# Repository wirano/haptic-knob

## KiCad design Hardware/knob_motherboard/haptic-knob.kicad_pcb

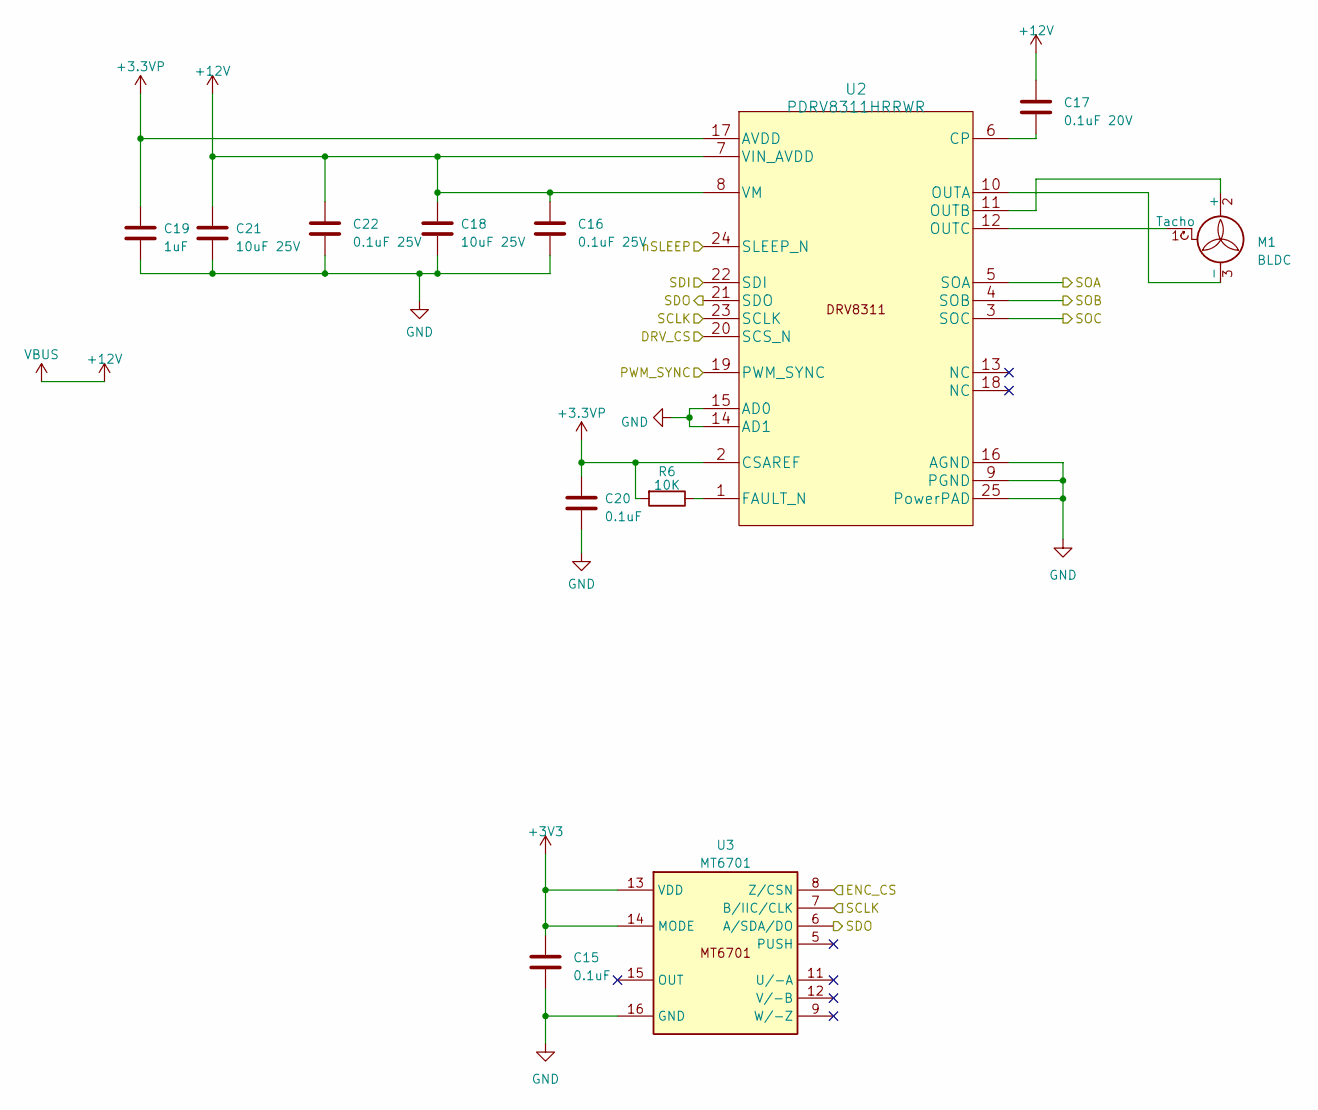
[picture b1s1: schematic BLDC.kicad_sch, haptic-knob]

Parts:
C15, C20: 0.1uF; C_0402_1005Metric
C16, C22: 0.1uF 25V; C_0402_1005Metric
C17: 0.1uF 20V; C_0402_1005Metric
C18, C21: 10uF 25V; C_0603_1608Metric
C19: 1uF; C_0402_1005Metric
M1: BLDC; JST_SH_BM03B-SRSS-TB_1x03-1MP_P1.00mm_Vertical
R6: 10K; R_0402_1005Metric
U2: PDRV8311HRRWR
U3: MT6701; QFN-16-1EP_3x3mm_P0.5mm_EP1.7x1.7mm

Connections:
+3.3VP: C19.1, C20.1, R6.2, U2.2 (CSAREF), U2.17 (AVDD)
+3V3: C15.1, U3.13 (VDD), U3.14 (MODE); also elsewhere on the board
+12V: C16.1, C17.1, C18.1, C21.1, C22.1, U2.7 (VIN_AVDD), U2.8 (VM); also elsewhere on the board
/BLDC/DRV_CS: U2.20 (SCS_N); also elsewhere on the board
/BLDC/ENC_CS: U3.8 (Z/CSN); also elsewhere on the board
/BLDC/PWM_SYNC: U2.19 (PWM_SYNC); also elsewhere on the board
/BLDC/SCLK: U2.23 (SCLK), U3.7 (B/IIC/CLK); also elsewhere on the board
/BLDC/SDI: U2.22 (SDI); also elsewhere on the board
/BLDC/SDO: U2.21 (SDO), U3.6 (A/SDA/DO); also elsewhere on the board
/BLDC/nSLEEP: U2.24 (SLEEP_N); also elsewhere on the board
/Core/SOA: U2.5 (SOA); also elsewhere on the board
/Core/SOB: U2.4 (SOB); also elsewhere on the board
/Core/SOC: U2.3 (SOC); also elsewhere on the board
GND: C15.2, C16.2, C18.2, C19.2, C20.2, C21.2, C22.2, M1.MP, U2.9 (PGND), U2.14 (AD1), U2.15 (AD0), U2.16 (AGND), U2.25 (PowerPAD), U2.26, U2.27, U2.28, U2.29, U2.30, U3.16 (GND), U3.17; also elsewhere on the board
unnamed: M1.2 (+), U2.11 (OUTB)
unnamed: M1.3 (-), U2.10 (OUTA)
unnamed: M1.1 (Tacho), U2.12 (OUTC)
unnamed: C17.2, U2.6 (CP)
unnamed: R6.1, U2.1 (FAULT_N)

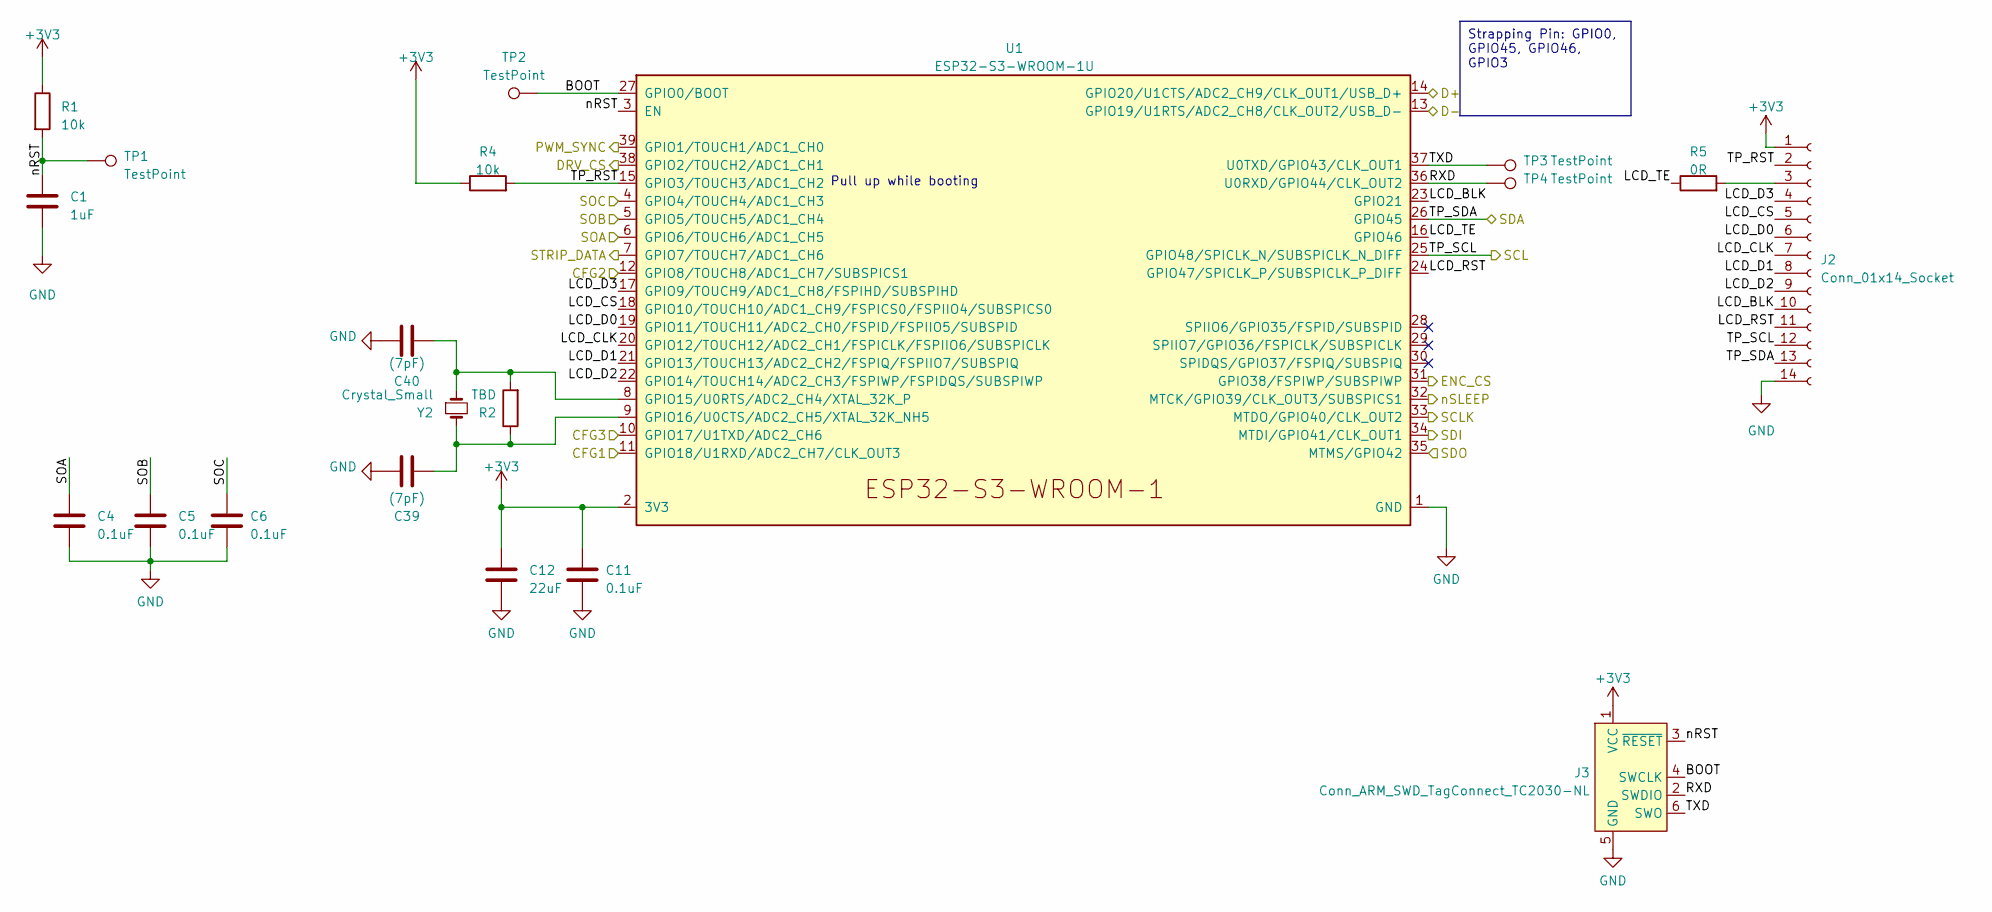
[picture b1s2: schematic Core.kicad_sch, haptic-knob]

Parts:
C1: 1uF; C_0402_1005Metric
C4, C5, C6, C11: 0.1uF; C_0402_1005Metric
C12: 22uF; C_0402_1005Metric
C39, C40: (7pF); C_0402_1005Metric
J2: Conn_01x14_Socket; JST_SHL_SM14B-SHLS-TF_1x14-1MP_P1.00mm_Horizontal
J3: Conn_ARM_SWD_TagConnect_TC2030-NL; Tag-Connect_TC2030-IDC-NL_2x03_P1.27mm_Vertical
R1, R4: 10k; R_0402_1005Metric
R2: TBD; R_0402_1005Metric
R5: 0R; R_0402_1005Metric
TP1, TP2, TP3, TP4: TestPoint; TestPoint_Pad_D1.5mm
U1: ESP32-S3-WROOM-1U
Y2: Crystal_Small; Crystal_SMD_2012-2Pin_2.0x1.2mm

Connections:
+3V3: C11.1, C12.1, J2.1, J3.1 (VCC), R1.1, R4.1, U1.2 (3V3); also elsewhere on the board
/BLDC/DRV_CS: U1.38 (GPIO2/TOUCH2/ADC1_CH1); also elsewhere on the board
/BLDC/ENC_CS: U1.31 (GPIO38/FSPIWP/SUBSPIWP); also elsewhere on the board
/BLDC/PWM_SYNC: U1.39 (GPIO1/TOUCH1/ADC1_CH0); also elsewhere on the board
/BLDC/SCLK: U1.33 (MTDO/GPIO40/CLK_OUT2); also elsewhere on the board
/BLDC/SDI: U1.34 (MTDI/GPIO41/CLK_OUT1); also elsewhere on the board
/BLDC/SDO: U1.35 (MTMS/GPIO42); also elsewhere on the board
/BLDC/nSLEEP: U1.32 (MTCK/GPIO39/CLK_OUT3/SUBSPICS1); also elsewhere on the board
/Core/BOOT: J3.4 (SWCLK), TP2.1, U1.27 (GPIO0/BOOT)
/Core/CFG1: U1.10 (GPIO17/U1TXD/ADC2_CH6); also elsewhere on the board
/Core/CFG2: U1.11 (GPIO18/U1RXD/ADC2_CH7/CLK_OUT3); also elsewhere on the board
/Core/CFG3: U1.12 (GPIO8/TOUCH8/ADC1_CH7/SUBSPICS1); also elsewhere on the board
/Core/D+: U1.14 (GPIO20/U1CTS/ADC2_CH9/CLK_OUT1/USB_D+); also elsewhere on the board
/Core/D-: U1.13 (GPIO19/U1RTS/ADC2_CH8/CLK_OUT2/USB_D-); also elsewhere on the board
/Core/LCD_BLK: J2.10, U1.23 (GPIO21)
/Core/LCD_CLK: J2.7, U1.20 (GPIO12/TOUCH12/ADC2_CH1/FSPICLK/FSPIIO6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)
/Core/LCD_CS: J2.5, U1.18 (GPIO10/TOUCH10/ADC1_CH9/FSPICS0/FSPIIO4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)
/Core/LCD_D0: J2.6, U1.19 (GPIO11/TOUCH11/ADC2_CH0/FSPID/FSPIIO5/S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)
/Core/LCD_D1: J2.8, U1.21 (GPIO13/TOUCH13/ADC2_CH2/FSPIQ/FSPIIO7/S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)
/Core/LCD_D2: J2.9, U1.22 (GPIO14/TOUCH14/ADC2_CH3/FSPIWP/FSPIDQS/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)
/Core/LCD_D3: J2.4, U1.17 (GPIO9/TOUCH9/ADC1_CH8/FSPIHD/SUBSPIHD)
/Core/LCD_RST: J2.11, U1.24 (GPIO47/SPICLK_P/SUBSPICLK_P_DIFF)
/Core/LCD_TE: R5.1, U1.16 (GPIO46)
/Core/RXD: J3.2 (SWDIO), TP4.1, U1.36 (U0RXD/GPIO44/CLK_OUT2)
/Core/SOA: C4.1, U1.6 (GPIO6/TOUCH6/ADC1_CH5); also elsewhere on the board
/Core/SOB: C5.1, U1.5 (GPIO5/TOUCH5/ADC1_CH4); also elsewhere on the board
/Core/SOC: C6.1, U1.4 (GPIO4/TOUCH4/ADC1_CH3); also elsewhere on the board
/Core/STRIP_DATA: U1.7 (GPIO7/TOUCH7/ADC1_CH6); also elsewhere on the board
/Core/TP_RST: J2.2, R4.2, U1.15 (GPIO3/TOUCH3/ADC1_CH2)
/Core/TP_SCL: J2.12, U1.25 (GPIO48/SPICLK_N/SUBSPICLK_N_DIFF); also elsewhere on the board
/Core/TP_SDA: J2.13, U1.26 (GPIO45); also elsewhere on the board
/Core/TXD: J3.6 (SWO), TP3.1, U1.37 (U0TXD/GPIO43/CLK_OUT1)
/Core/nRST: C1.1, J3.3 (~RESET), R1.2, TP1.1, U1.3 (EN)
GND: C1.2, C4.2, C5.2, C6.2, C11.2, C12.2, J2.14, J2.MP, J3.5 (GND), U1.1 (GND), U1.40 (GND), U1.41 (GND); also elsewhere on the board
unnamed: J2.3, R5.2
unnamed 49: R2.2, U1.8 (GPIO15/U0RTS/ADC2_CH4/XTAL_32K_P); also elsewhere on the board
unnamed 50: R2.1, U1.9 (GPIO16/U0CTS/ADC2_CH5/XTAL_32K_NH5); also elsewhere on the board

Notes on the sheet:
Strapping Pin: GPIO0, GPIO45, GPIO46, GPIO3
Pull up while booting

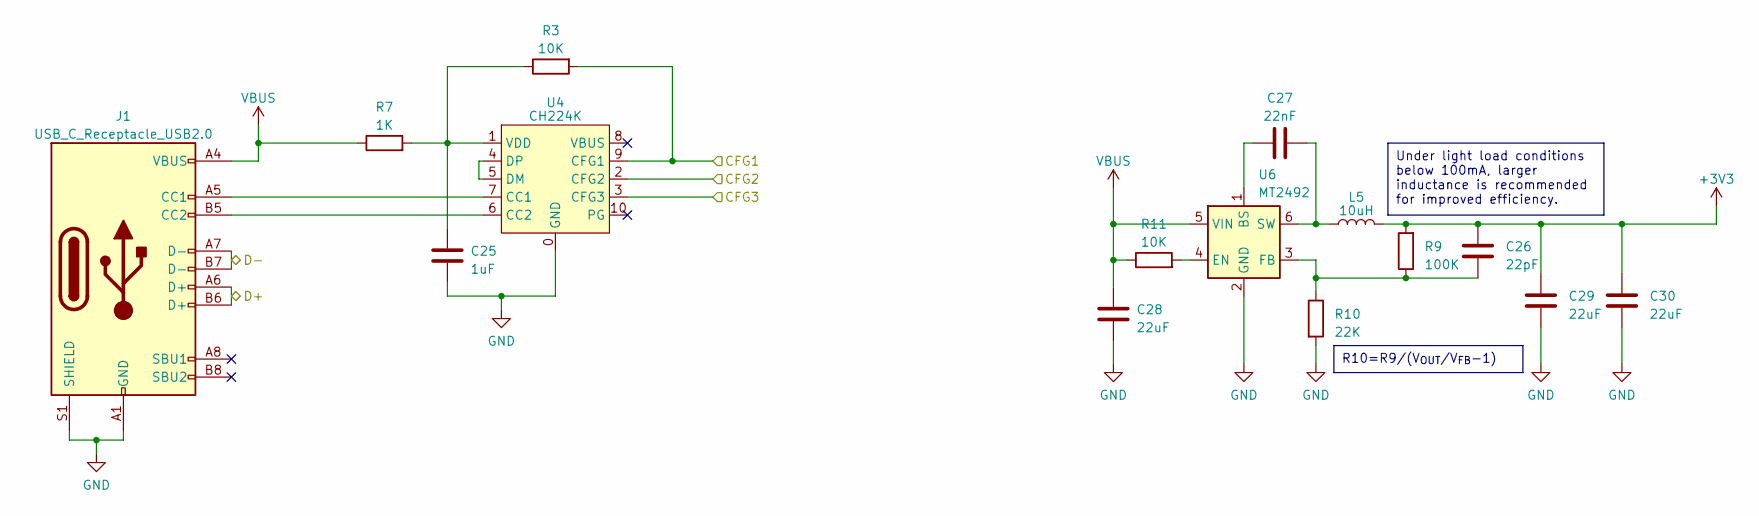
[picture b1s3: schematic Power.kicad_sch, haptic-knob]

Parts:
C25: 1uF; C_0402_1005Metric
C26: 22pF; C_0402_1005Metric
C27: 22nF; C_0402_1005Metric
C28, C29, C30: 22uF; C_0805_2012Metric
J1: USB_C_Receptacle_USB2.0; USB_C_Receptacle_XKB_U262-16XN-4BVC11
L5: 10uH; L_Sunlord_SWPA3015S
R3, R11: 10K; R_0402_1005Metric
R7: 1K; R_0402_1005Metric
R9: 100K; R_0402_1005Metric
R10: 22K; R_0402_1005Metric
U4: CH224K; ESSOP-10_3.9x4.9mm_P1.00mm_EP2.3x3.2mm
U6: MT2492; SOT-23-6

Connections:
+3V3: C26.2, C29.1, C30.1, L5.2, R9.2; also elsewhere on the board
+12V: C28.1, J1.A4 (VBUS), J1.A9 (VBUS), J1.B4 (VBUS), J1.B9 (VBUS), R7.1, R11.1, U6.5 (VIN); also elsewhere on the board
/Core/CFG1: R3.2, U4.9 (CFG1); also elsewhere on the board
/Core/CFG2: U4.2 (CFG2); also elsewhere on the board
/Core/CFG3: U4.3 (CFG3); also elsewhere on the board
/Core/D+: J1.A6 (D+), J1.B6 (D+); also elsewhere on the board
/Core/D-: J1.A7 (D-), J1.B7 (D-); also elsewhere on the board
GND: C25.2, C28.2, C29.2, C30.2, J1.A1 (GND), J1.A12 (GND), J1.B1 (GND), J1.B12 (GND), J1.S1 (SHIELD), R10.2, U4.0 (GND), U6.2 (GND); also elsewhere on the board
unnamed: J1.A5 (CC1), U4.7 (CC1)
unnamed: J1.B5 (CC2), U4.6 (CC2)
unnamed: U4.4 (DP), U4.5 (DM)
unnamed: C25.1, R3.1, R7.2, U4.1 (VDD)
unnamed: C27.1, U6.1 (BS)
unnamed: R11.2, U6.4 (EN)
unnamed: C26.1, R9.1, R10.1, U6.3 (FB)
unnamed: C27.2, L5.1, U6.6 (SW)

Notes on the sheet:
R10=R9/(V_{OUT}/V_{FB}-1)
Under light load conditions below 100mA, larger inductance is recommended for improved efficiency.

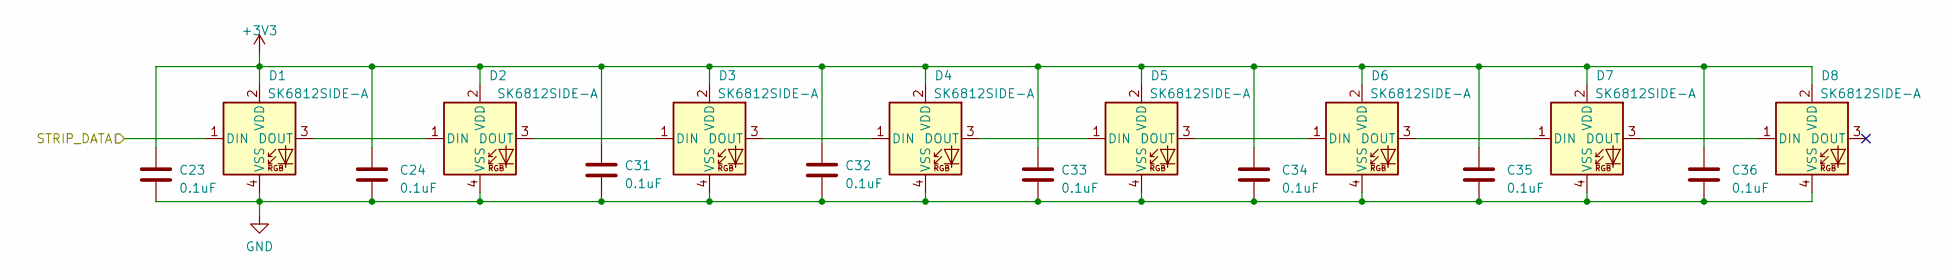
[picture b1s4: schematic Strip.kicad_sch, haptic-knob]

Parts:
C23, C24, C31, C32, C33, C34, C35, C36: 0.1uF; C_0402_1005Metric
D1, D2, D3, D4, D5, D6, D7, D8: SK6812SIDE-A; SK6812D-EC3210R

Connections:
+3V3: C23.1, C24.1, C31.1, C32.1, C33.1, C34.1, C35.1, C36.1, D1.2 (VDD), D2.2 (VDD), D3.2 (VDD), D4.2 (VDD), D5.2 (VDD), D6.2 (VDD), D7.2 (VDD), D8.2 (VDD); also elsewhere on the board
/Core/STRIP_DATA: D1.1 (DIN); also elsewhere on the board
GND: C23.2, C24.2, C31.2, C32.2, C33.2, C34.2, C35.2, C36.2, D1.4 (VSS), D2.4 (VSS), D3.4 (VSS), D4.4 (VSS), D5.4 (VSS), D6.4 (VSS), D7.4 (VSS), D8.4 (VSS); also elsewhere on the board
unnamed: D1.3 (DOUT), D2.1 (DIN)
unnamed: D2.3 (DOUT), D3.1 (DIN)
unnamed: D3.3 (DOUT), D4.1 (DIN)
unnamed: D4.3 (DOUT), D5.1 (DIN)
unnamed: D5.3 (DOUT), D6.1 (DIN)
unnamed: D6.3 (DOUT), D7.1 (DIN)
unnamed: D7.3 (DOUT), D8.1 (DIN)

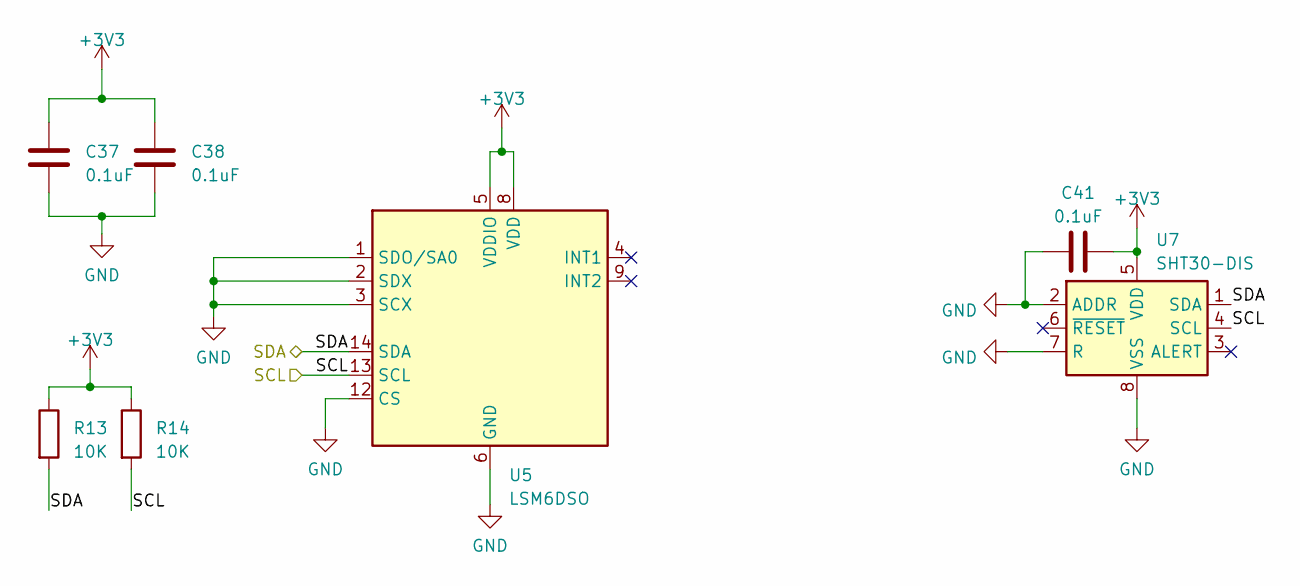
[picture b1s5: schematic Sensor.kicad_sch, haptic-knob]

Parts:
C37, C38, C41: 0.1uF; C_0402_1005Metric
R13, R14: 10K; R_0402_1005Metric
U5: LSM6DSO; LGA-14_3x2.5mm_P0.5mm_LayoutBorder3x4y
U7: SHT30-DIS; Sensirion_DFN-8-1EP_2.5x2.5mm_P0.5mm_EP1.1x1.7mm

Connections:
+3V3: C37.1, C38.1, C41.2, R13.1, R14.1, U5.5 (VDDIO), U5.8 (VDD), U7.5 (VDD); also elsewhere on the board
/Core/TP_SCL: R14.2, U5.13 (SCL), U7.4 (SCL); also elsewhere on the board
/Core/TP_SDA: R13.2, U5.14 (SDA), U7.1 (SDA); also elsewhere on the board
GND: C37.2, C38.2, C41.1, U5.1 (SDO/SA0), U5.2 (SDX), U5.3 (SCX), U5.6 (GND), U5.7 (GND), U5.12 (CS), U7.2 (ADDR), U7.7 (R), U7.8 (VSS), U7.9 (VSS); also elsewhere on the board

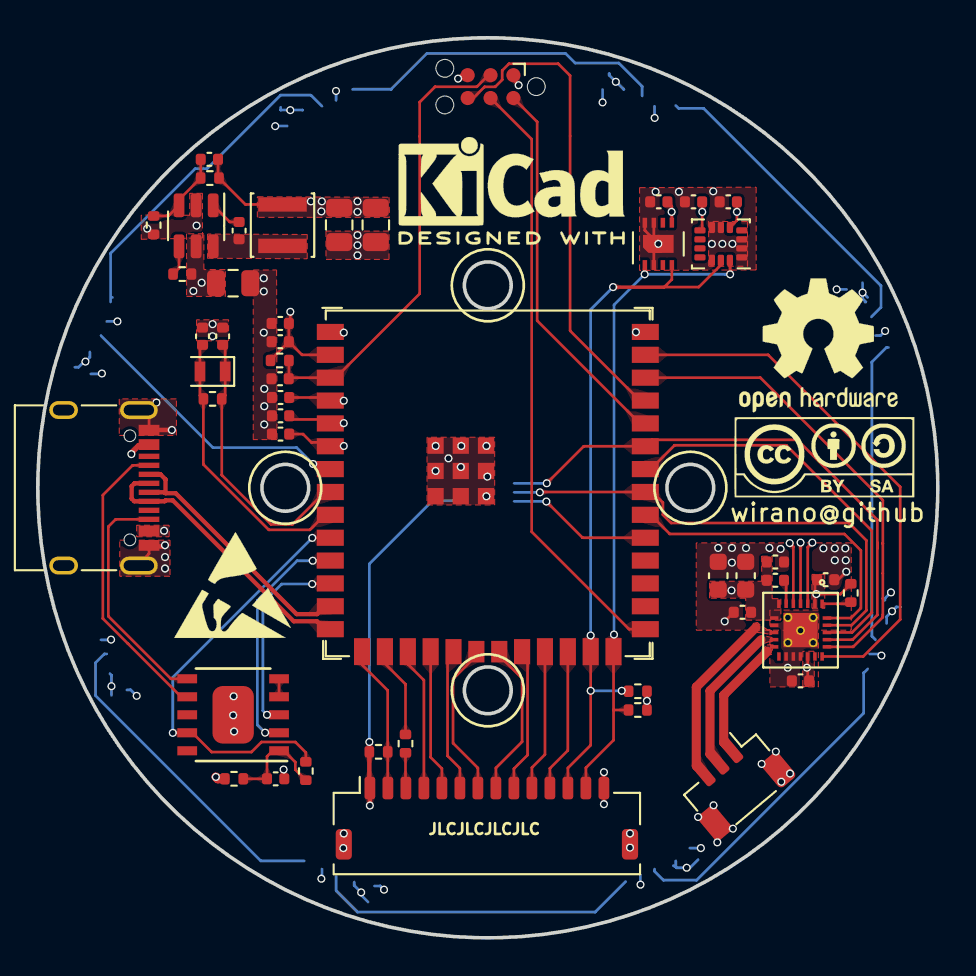
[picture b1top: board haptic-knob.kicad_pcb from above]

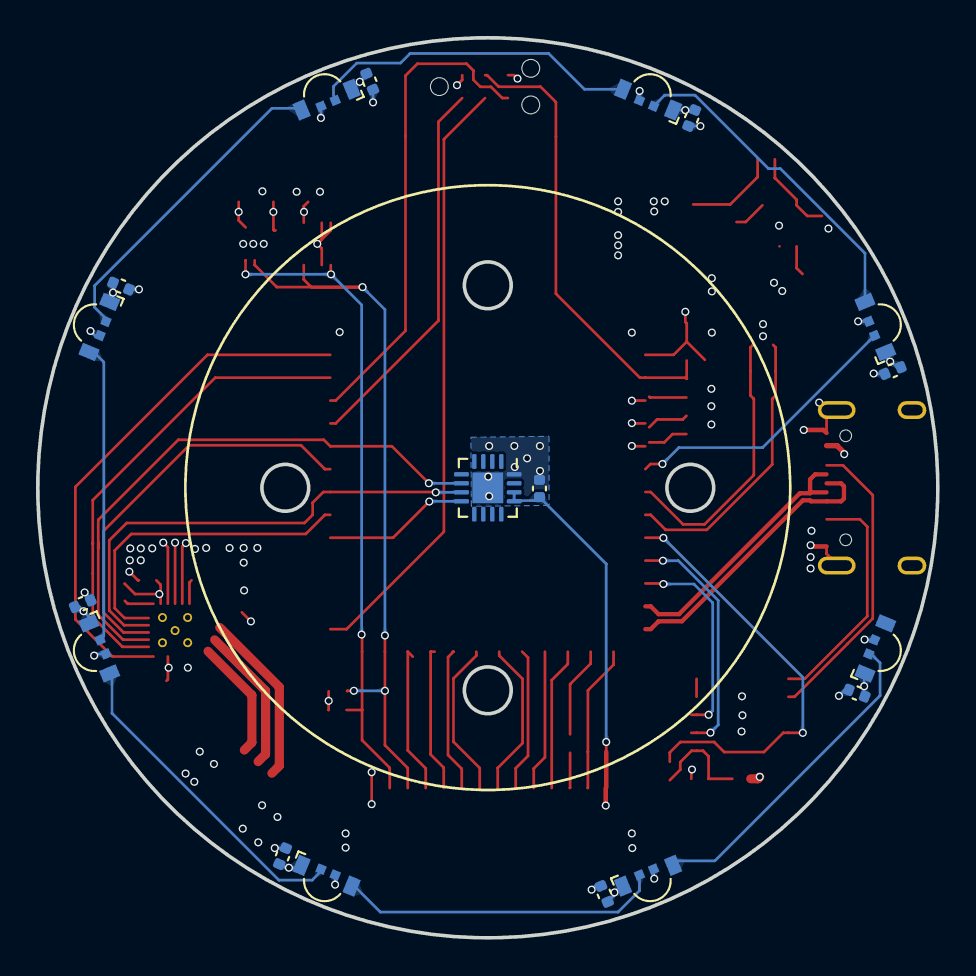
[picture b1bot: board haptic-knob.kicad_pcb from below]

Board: 4 copper layers, 50.0 x 50.0 mm, 66 parts (18 on the bottom side), 59 nets.

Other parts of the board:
C2, C3: (7pF); C_0402_1005Metric
Y1: Crystal_Small; Crystal_SMD_2012-2Pin_2.0x1.2mm

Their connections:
GND: C2.2, C3.2; also elsewhere on the board
unnamed 49: C3.1, Y1.1; also elsewhere on the board
unnamed 50: C2.1, Y1.2; also elsewhere on the board

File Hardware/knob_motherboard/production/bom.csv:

Designator,Footprint,Quantity,Value,LCSC Part #
C1,0402,1,1uF,
C11,0402,1,0.1uF,
C12,0402,1,22uF,
C15,0402,1,0.1uF,
C16,0402,1,0.1uF 25V,
C17,0402,1,0.1uF 20V,
C18,0603,1,10uF 25V,
C19,0402,1,1uF,
C2,0402,1,(7pF),
C20,0402,1,0.1uF,
C21,0603,1,10uF 25V,
C22,0402,1,0.1uF 25V,
C23,0402,1,0.1uF,
C24,0402,1,0.1uF,
C25,0402,1,1uF,
C26,0402,1,22pF,
C27,0402,1,22nF,
C28,0805,1,22uF,
C29,0805,1,22uF,
C3,0402,1,(7pF),
C30,0805,1,22uF,
C31,0402,1,0.1uF,
C32,0402,1,0.1uF,
C33,0402,1,0.1uF,
C34,0402,1,0.1uF,
C35,0402,1,0.1uF,
C36,0402,1,0.1uF,
C37,0402,1,0.1uF,
C38,0402,1,0.1uF,
C4,0402,1,0.1uF,
C41,0402,1,0.1uF,
C5,0402,1,0.1uF,
C6,0402,1,0.1uF,
"D1, D2, D3, D4, D5, D6, D7, D8",SK6812D-EC3210R,8,SK6812SIDE-A,
J1,USB_C_Receptacle_XKB_U262-16XN-4BVC11,1,USB_C_Receptacle_USB2.0,
J2,JST_SHL_SM14B-SHLS-TF_1x14-1MP_P1.00mm_Horizontal,1,Conn_01x14_Socket,
J3,Tag-Connect_TC2030-IDC-NL_2x03_P1.27mm_Vertical,1,Conn_ARM_SWD_TagConnect_TC2030-NL,
L5,L_Sunlord_SWPA3015S,1,10uH,
M1,JST_SH_BM03B-SRSS-TB_1x03-1MP_P1.00mm_Vertical,1,BLDC,
R1,0402,1,10k,
R10,0402,1,22K,
R11,0402,1,10K,
R13,0402,1,10K,
R14,0402,1,10K,
R2,0402,1,TBD,
R3,0402,1,10K,
R4,0402,1,10k,
R5,0402,1,0R,
R6,0402,1,10K,
R7,0402,1,1K,
R9,0402,1,100K,
"TP1, TP2, TP3, TP4",TestPoint_Pad_D1.5mm,4,TestPoint,
U1,ESP32-S3-WROOM-1U,1,ESP32-S3-WROOM-1U,
U2,PDRV8311HRRWR,1,PDRV8311HRRWR,
U3,QFN-16-1EP_3x3mm_P0.5mm_EP1.7x1.7mm,1,MT6701,
U4,ESSOP-10_3.9x4.9mm_P1.00mm_EP2.3x3.2mm,1,CH224K,
U5,LGA-14_3x2.5mm_P0.5mm_LayoutBorder3x4y,1,LSM6DSO,
U6,SOT-23-6,1,MT2492,
U7,Sensirion_DFN-8-1EP_2.5x2.5mm_P0.5mm_EP1.1x1.7mm,1,SHT30-DIS,
Y1,Crystal_SMD_2012-2Pin_2.0x1.2mm,1,Crystal_Small,

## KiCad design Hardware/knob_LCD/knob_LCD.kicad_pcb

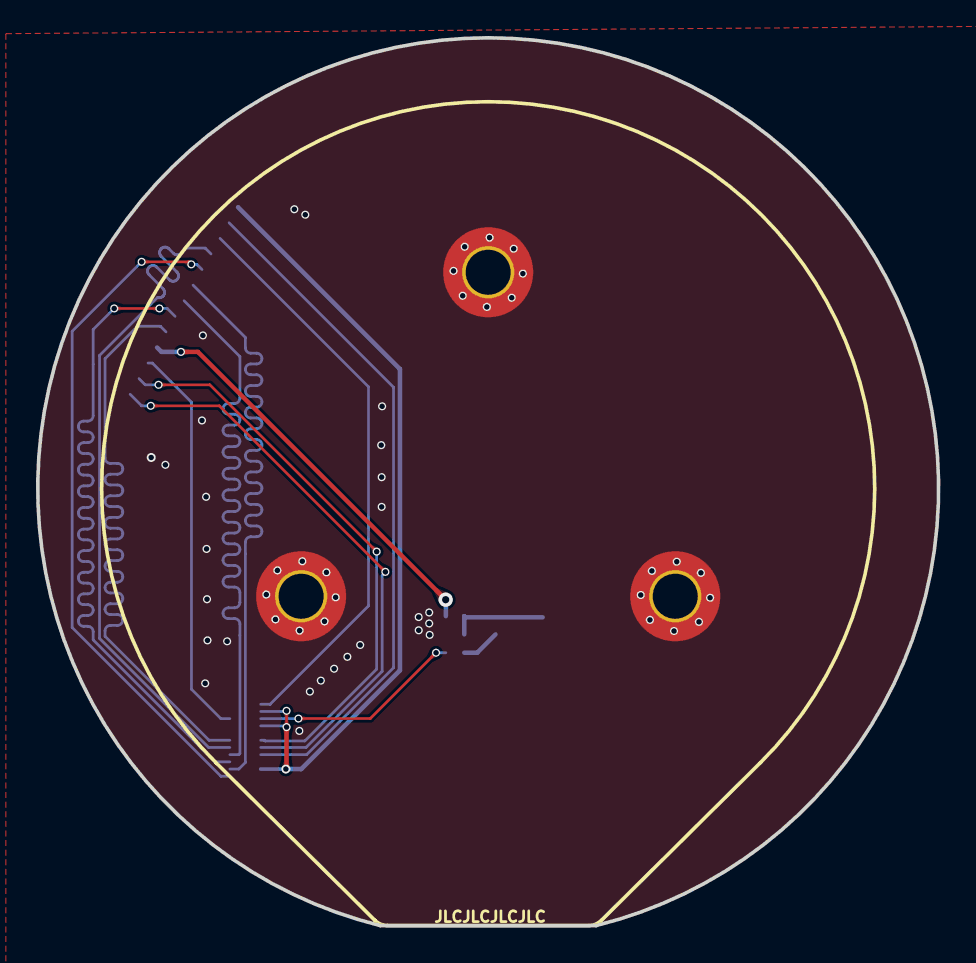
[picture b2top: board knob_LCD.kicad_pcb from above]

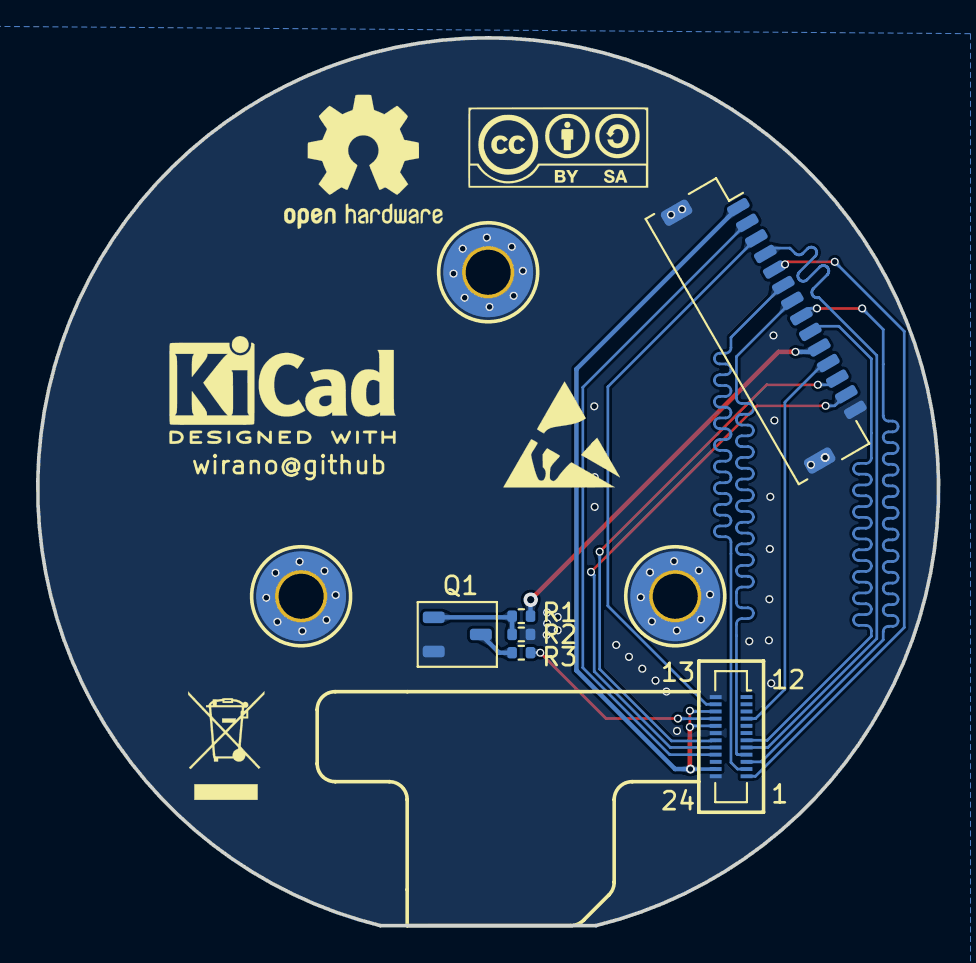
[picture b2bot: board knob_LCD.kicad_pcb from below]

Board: 2 copper layers, 50.0 x 49.3 mm, 9 parts (6 on the bottom side), 17 nets.

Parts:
H1, H2, H3: MountingHole_Pad; MountingHole_2.5mm_Pad_TopBottom
J1: ST77903; Molex_SlimStack_502430-2410_2x12_P0.40mm_Vertical
J3: Conn_01x14_Socket; JST_SHL_SM14B-SHLS-TF_1x14-1MP_P1.00mm_Horizontal
Q1: AO3400A; TSOT-23
R1: 100R; R_0402_1005Metric
R2: 10K; R_0402_1005Metric
R3: 10R; R_0402_1005Metric

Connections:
+3V3: J1.15 (VCC), J1.17 (LEDA), J1.23 (TP_VDD), J3.1
/LCD_BLK: J3.10, R1.1
/LCD_CLK: J1.4 (CLK), J3.7
/LCD_CS: J1.1 (CS), J3.5
/LCD_D0: J1.2 (IO0), J3.6
/LCD_D1: J1.3 (IO1), J3.8
/LCD_D2: J1.6 (IO2), J3.9
/LCD_D3: J1.5 (IO3), J3.4
/LCD_RST: J1.9 (RST), J3.11
/LCD_TE: J1.14 (TE), J3.3
/LEDK: J1.16 (LEDK), R3.1
/TP_RST: J1.21 (TP_RST), J3.2
/TP_SCL: J1.19 (TP_SCL), J3.12
/TP_SDA: J1.20 (TP_SDA), J3.13
GND: H1.1, H2.1, H3.1, J1.13 (GND), J1.18 (GND), J1.24 (GND), J3.14, J3.MP, Q1.2 (S), R2.2
unnamed: Q1.3 (D), R3.2
unnamed: Q1.1 (G), R1.2, R2.1

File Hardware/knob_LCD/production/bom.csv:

Designator,Footprint,Quantity,Value,LCSC Part #
"H1, H2, H3",MountingHole_2.5mm_Pad_TopBottom,3,MountingHole_Pad,
J1,Molex_SlimStack_502430-2410_2x12_P0.40mm_Vertical,1,ST77903,
J3,JST_SHL_SM14B-SHLS-TF_1x14-1MP_P1.00mm_Horizontal,1,Conn_01x14_Socket,
Q1,TSOT-23,1,AO3400A,
R1,0402,1,100R,
R2,0402,1,10K,
R3,0402,1,10R,

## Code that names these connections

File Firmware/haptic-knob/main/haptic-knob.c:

#include "driver/gpio.h"
#include "esp_log.h"
#include "freertos/FreeRTOS.h"
#include "freertos/task.h"
#include "nvs_flash.h"

#include "lv_port.h"
#include "knob_task.h"
#include "wifi.h"
#include "mqtt.h"

#define CFG1    17U
#define CFG2    18U
#define CFG3    8U

#define TAG "main"

void app_main(void) {
    gpio_config_t gpio_conf;

    gpio_conf.mode = GPIO_MODE_OUTPUT;
    gpio_conf.intr_type = GPIO_INTR_DISABLE;
    gpio_conf.pull_up_en = false;
    gpio_conf.pull_down_en = false;
    gpio_conf.pin_bit_mask = 1 << CFG1;
    gpio_config(&gpio_conf);

    gpio_conf.pin_bit_mask = 1 << CFG2;
    gpio_config(&gpio_conf);

    gpio_conf.pin_bit_mask = 1 << CFG3;
    gpio_config(&gpio_conf);

    // 12V
    gpio_set_level(CFG2, 0);
    gpio_set_level(CFG3, 1);
    gpio_set_level(CFG1, 0);

    nvs_flash_init();

//    wifi_init_sta();

//    mqtt_app_start();

    lvgl_init();

    knob_task_init();

    vTaskDelete(NULL);
}

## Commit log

2023-04-01 init
2023-04-03 start firmware
2023-04-03 modified pin
2023-04-03 fix socket pinout
2023-04-05 drv8311 spi bugfix & ch224k CFG1 bugfix
2023-04-05 drv8311: first version
2023-04-07 mt6701: first version
2023-04-11 bom export
2023-04-11 CH224K & ST77903 symbol fix
2023-04-12 change pin num
2023-04-13 mt6701: read data from chip
2023-04-13 drv8311: turn reg define to little-endian
2023-04-14 invert drv8311 transmit package
2023-04-14 drv8311: read data from drv8311
2023-04-15 generate MCPWM for PWM SYNC; tuning drv8311 timing
2023-04-16 drv8311: add workaround for rec timing error
2023-04-17 drv8311: add some interface
2023-04-18 add pid
2023-04-19 sdd svpwm
2023-04-20 rename function
2023-04-20 retrun angle in radian
2023-04-20 more work
2023-04-20 add adc current sample
2023-04-21 make current sense work
2023-04-21 not work
2023-04-26 add api
2023-04-26 add console
2023-04-28 add cmd
2023-04-28 bug fix
2023-04-29 add deinit
2023-05-01 use simpleFOC's pid
2023-05-04 add deadzone
2023-05-04 add knob
2023-05-04 add new api
2023-05-04 new way to flush screen
2023-05-04 add encoder & ui
2023-05-04 add squareline ui
2023-05-05 ui update
2023-05-05 update ui
2023-05-06 add wifi&mqtt
2023-05-06 add light control via mqtt
2023-05-07 switch to new pid controler
2023-05-07 the most foolish thing
2023-05-08 correct phase order
2023-05-08 add switch mode

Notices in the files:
parts and their libraries:
Copyright 2021 Accelerated Designs. All rights reserved.
